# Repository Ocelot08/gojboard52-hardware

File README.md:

# gojboard52 hardware

Hardware files for **gojboard52**, a split wireless keyboard built around two nice!nano v2 controllers. The right
half carries a capacitive touch-bar slider (Microchip AT42QT2120); the left half carries a nice!view display
(an OLED footprint is also on the board).

Firmware lives in its own repository: https://github.com/Ocelot08/gojboard52-zmk

> Work in progress. Build notes are still to come.

## Photos

| | |
| --- | --- |
|  |  |

## Contents

| Folder | What is in it |
| --- | --- |
| `pcb/main-board/` | Keyboard PCB, KiCad 10 project (`BTSplit.kicad_pro`), STEP model, and fabrication gerbers (`gerber/`, zipped as `GojBoardV2-2_gerbers.zip`) |
| `pcb/touch-bar/` | Touch-bar PCB, KiCad project (`BTSplit_Touch.kicad_pro`), STEP model, and gerbers (`gerber/`, zipped as `GBTouchV0-3_gerbers.zip`) |
| `pcb/libs/` | The custom symbols and footprints these boards use (the double-sided SMD footprints, the pro micro and OLED footprints, the logo graphics) |
| `case/step/` | Case top and bottom (V4b) and a test plate, as STEP |
| `case/stl/` | Printable support parts: touch-bar support, nice!view support, alignment frame |
| `case/keycaps/` | Blank keycap and layer/mod keycap models |
| `docs/` | AT42QT2120 datasheet |
| `photos/` | The photos shown in this README |

The editable Rhino (`.3dm`) case models are not in this repository because of their size (40 MB or more each).

## PCB notes

- Project files are named `BTSplit` from the project's earlier name. The board is the gojboard52.
- Main board: 28 switch positions per board (Kailh low-profile, reversible footprint), through-hole diodes,
  1206 hand-solder resistors and capacitors, a pro-micro-pattern socket for the nice!nano, and double-sided SMD
  footprints (reset switch, power switch, resistors, capacitors) so they can be placed on either side.
- Reset switch: Panasonic EVQ-PUA02K. Power switch: Alps SSSS811101.
- Touch bar: three-electrode slider mode, six 1206 resistors, all 4.7 kΩ as built.
- Schematics and boards embed the symbols and footprints they use, so the projects open without extra setup. To edit
  parts, add `pcb/libs/01_Symbols.kicad_sym` and `pcb/libs/gojboard52.pretty` as libraries in KiCad.
- The BOM CSV exported from KiCad is out of date and is not included.

## Ordering

Upload the gerber zip for the board to the PCB fab of your choice (1.6 mm, 2 layers).

## License

Not yet chosen.

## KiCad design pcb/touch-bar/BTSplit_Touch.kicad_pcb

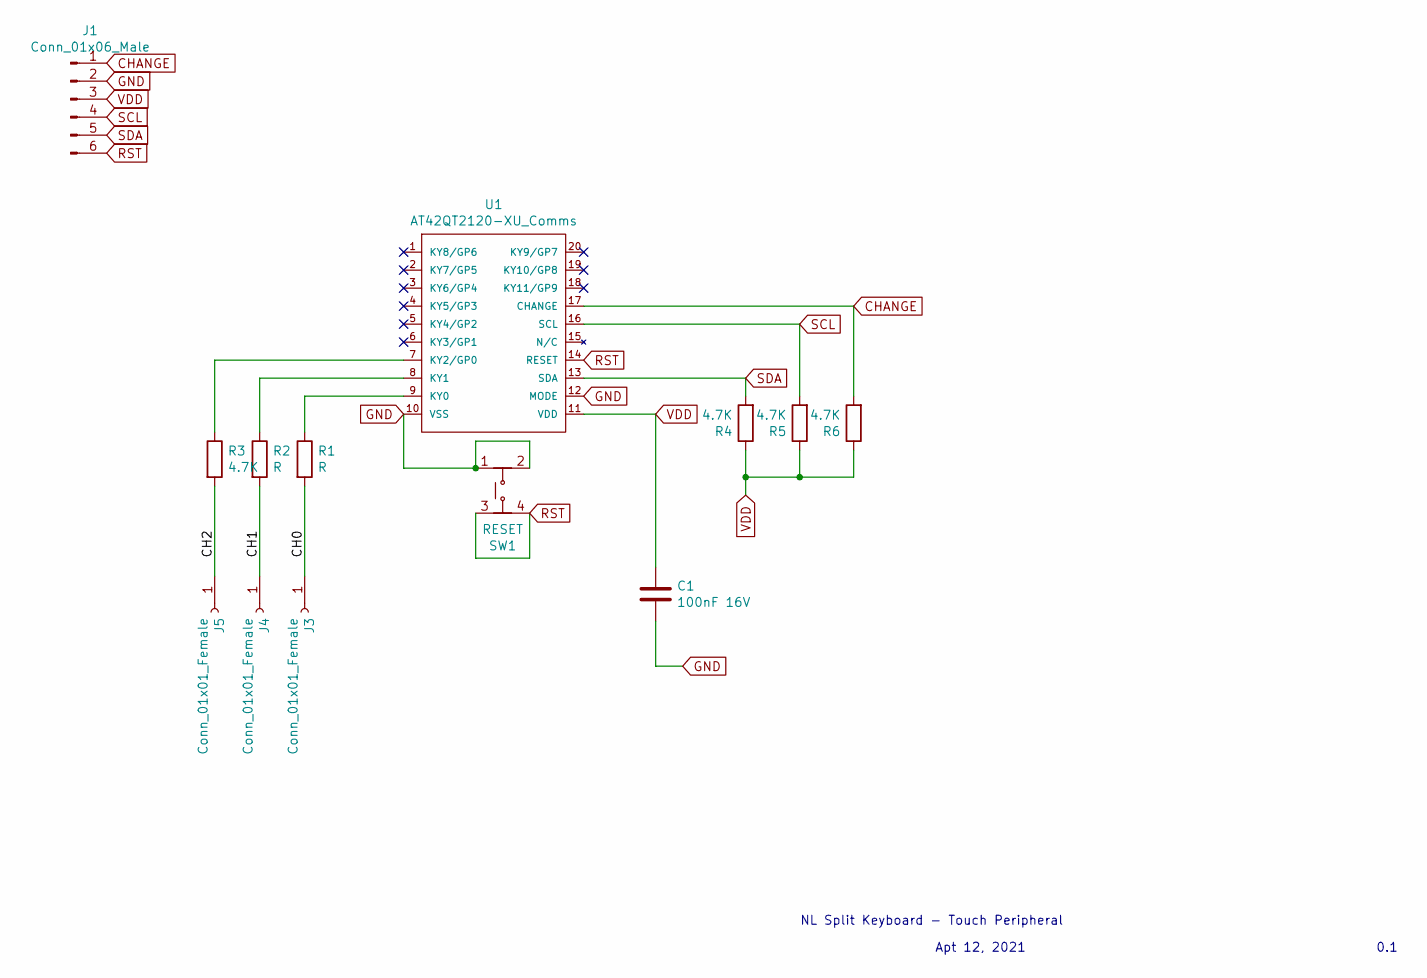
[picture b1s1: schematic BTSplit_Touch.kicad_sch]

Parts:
C1: 100nF 16V; C_1206_3216Metric
J1: Conn_01x06_Male; PinHeader_1x06_P2.54mm_Vertical
J3, J4, J5: Conn_01x01_Female; 1pad
R1, R2: R; R_1206_3216Metric_Pad1.30x1.75mm_HandSolder
R3, R4, R5, R6: 4.7K; R_1206_3216Metric_Pad1.30x1.75mm_HandSolder
SW1: RESET; PTS526 Switch
U1: AT42QT2120-XU_Comms; AT42QT2120-XUR

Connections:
/CH0: J3.1 (Pin_1_1), R1.2
/CH1: J4.1 (Pin_1_1), R2.2
/CH2: J5.1 (Pin_1_1), R3.2
CHANGE: J1.1, R6.2, U1.17 (CHANGE)
GND: C1.2, J1.2, SW1.1, SW1.2, U1.10 (VSS), U1.12 (MODE)
unnamed: R1.1, U1.9 (KY0)
unnamed: R2.1, U1.8 (KY1)
unnamed: R3.1, U1.7 (KY2/GP0)
RST: J1.6, SW1.3, SW1.4, U1.14 (RESET)
SCL: J1.4, R5.2, U1.16 (SCL)
SDA: J1.5, R4.2, U1.13 (SDA)
VDD: C1.1, J1.3, R4.1, R5.1, R6.1, U1.11 (VDD)

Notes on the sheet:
0.1
Apt 12, 2021
NL Split Keyboard - Touch Peripheral

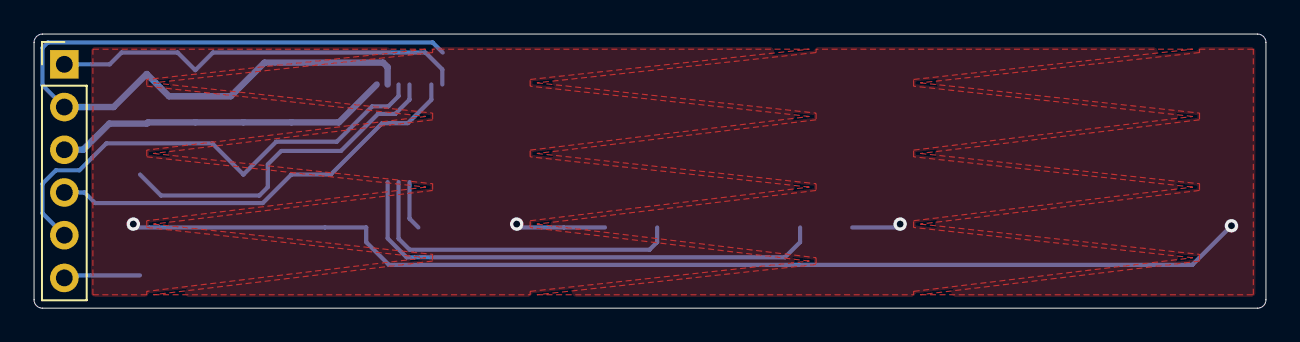
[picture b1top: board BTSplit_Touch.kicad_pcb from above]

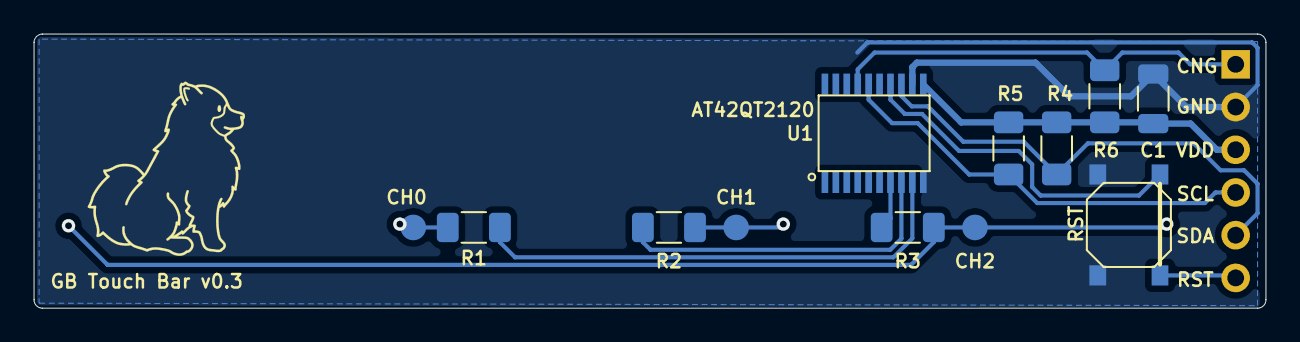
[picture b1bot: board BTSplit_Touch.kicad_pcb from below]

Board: 2 copper layers, 73.2 x 16.3 mm, 14 parts (13 on the bottom side), 12 nets.

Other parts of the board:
G2: Graphic; Goji10

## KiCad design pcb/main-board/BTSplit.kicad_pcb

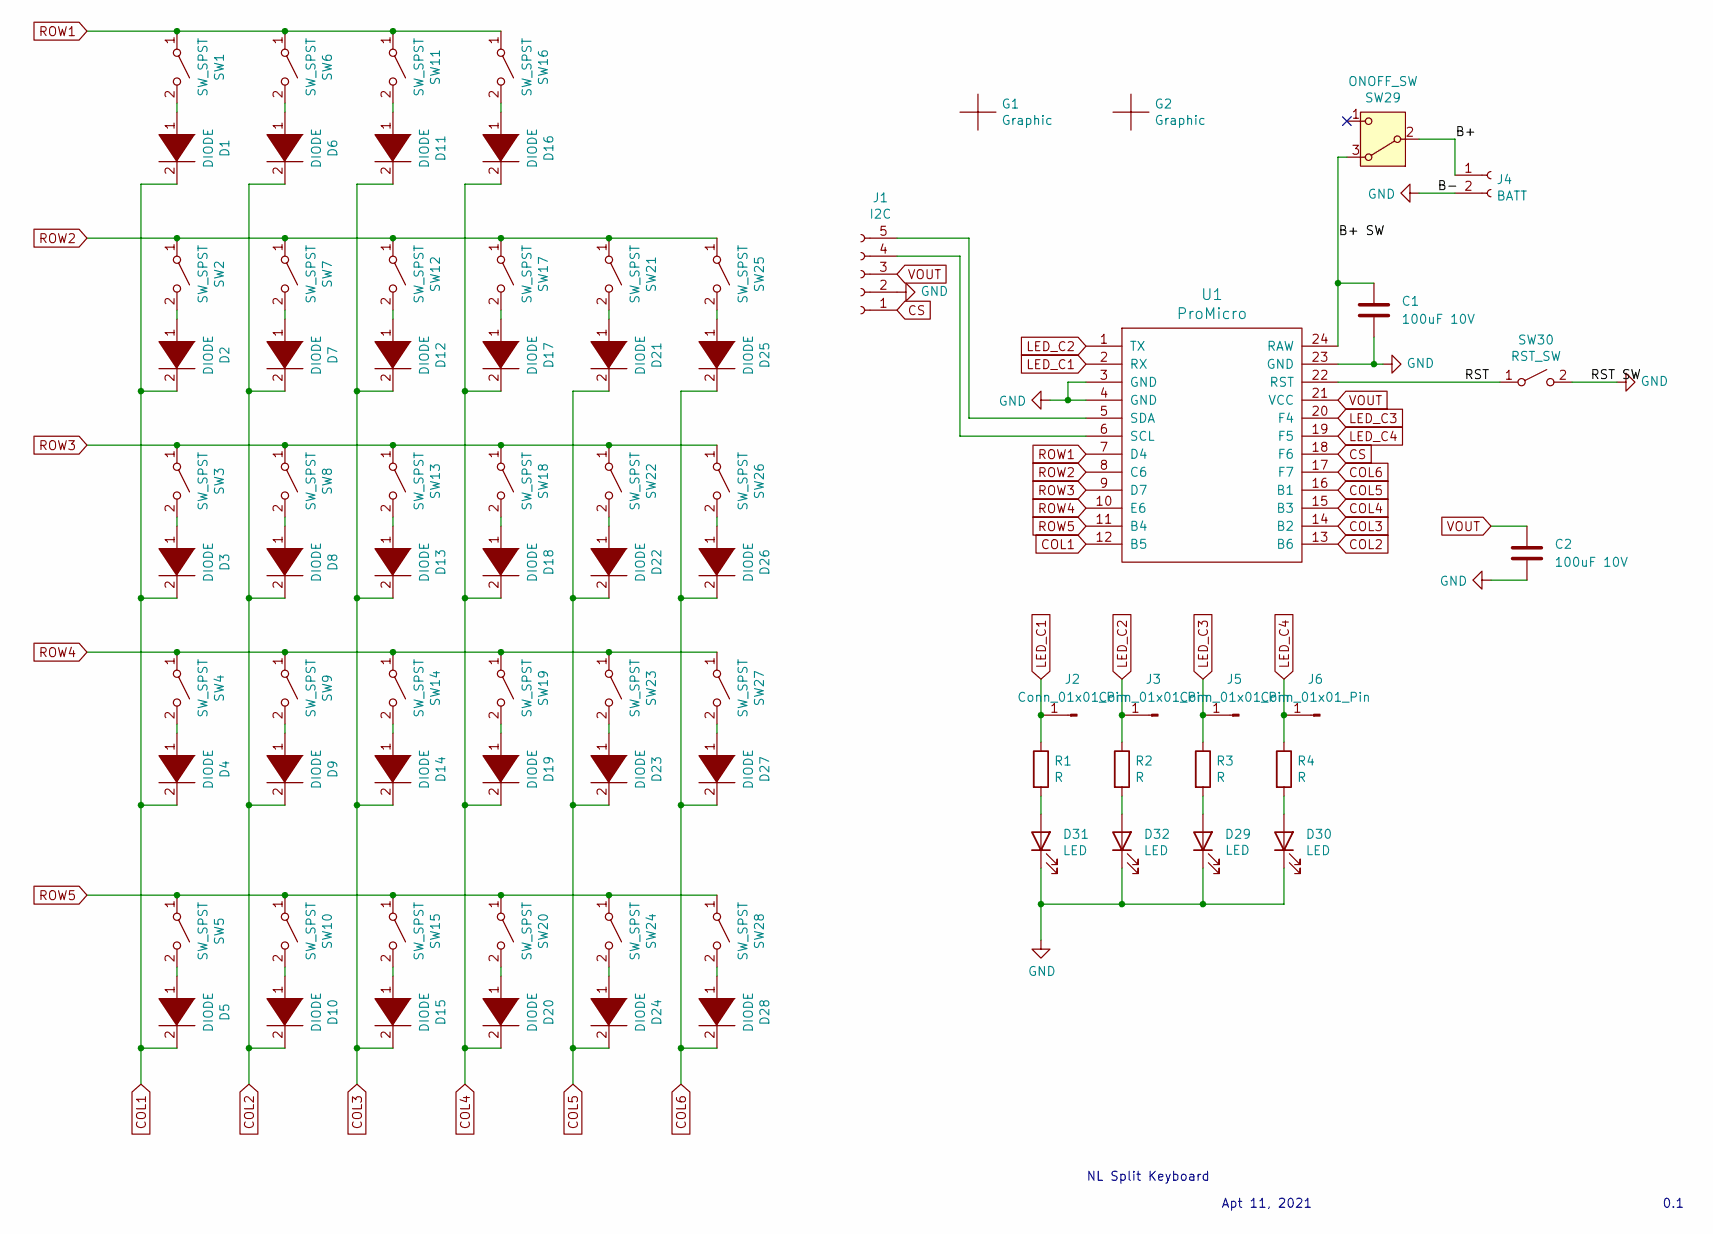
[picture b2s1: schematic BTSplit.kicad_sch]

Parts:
C1, C2: 100uF 10V; C_1206_HandSolder_DoubleSided
D1, D2, D3, D4, D5, D6, D7, D8, D9, D10, D11, D12, D13, D14, D15, D16, D17, D18, D19, D20, D21, D22, D23, D24, D25, D26, D27, D28: DIODE; D_DO-35_SOD27_P7.62mm_Horizontal
D29, D30, D31, D32: LED; LED_D1.8mm_W3.3mm_H2.4mm
G1: Graphic; Goji15
G2: Graphic; Goj30
J1: I2C; PinSocket_1x05_P2.54mm_Vertical
J2, J3, J5, J6: Conn_01x01_Pin; 1pad_DoubleSided
J4: BATT; PinHeader_1x02_P2.00mm_Vertical
R1, R2, R3, R4: R; R_1206_HandSolder_DoubleSided
SW1, SW2, SW3, SW4, SW5, SW6, SW7, SW8, SW9, SW10, SW11, SW12, SW13, SW14, SW15, SW16, SW17, SW18, SW19, SW20, SW21, SW22, SW23, SW24, SW25, SW26, SW27, SW28: SW_SPST; SW_Kailh_Choc_V1V2_flip
SW29: ONOFF_SW; SW4_SSSS811101_ALPS_DoubleSided
SW30: RST_SW; Panasonic_EVQPUJ_EVQPUA_DoubleSided
U1: ProMicro; ArduinoProMicro

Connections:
/B+: J4.1, SW29.2 (B)
/B+ SW: C1.1, SW29.3 (A), U1.24 (RAW)
/RST: SW30.1 (A), U1.22 (RST)
COL1: D1.2 (A), D2.2 (A), D3.2 (A), D4.2 (A), D5.2 (A), U1.12 (B5)
COL2: D6.2 (A), D7.2 (A), D8.2 (A), D9.2 (A), D10.2 (A), U1.13 (B6)
COL3: D11.2 (A), D12.2 (A), D13.2 (A), D14.2 (A), D15.2 (A), U1.14 (B2)
COL4: D16.2 (A), D17.2 (A), D18.2 (A), D19.2 (A), D20.2 (A), U1.15 (B3)
COL5: D21.2 (A), D22.2 (A), D23.2 (A), D24.2 (A), U1.16 (B1)
COL6: D25.2 (A), D26.2 (A), D27.2 (A), D28.2 (A), U1.17 (F7)
CS: J1.1, U1.18 (F6)
GND: C1.2, C2.2, D29.1 (K), D30.1 (K), D31.1 (K), D32.1 (K), J1.2, J4.2, SW30.2 (B), U1.3 (GND), U1.4 (GND), U1.23 (GND)
LED_C1: J2.1 (Pin_1_1), R1.1, U1.2 (RX)
LED_C2: J3.1 (Pin_1_1), R2.1, U1.1 (TX)
LED_C3: J5.1 (Pin_1_1), R3.1, U1.20 (F4)
LED_C4: J6.1 (Pin_1_1), R4.1, U1.19 (F5)
unnamed: D1.1 (K), SW1.2 (B)
unnamed: D2.1 (K), SW2.2 (B)
unnamed: D3.1 (K), SW3.2 (B)
unnamed: D4.1 (K), SW4.2 (B)
unnamed: D5.1 (K), SW5.2 (B)
unnamed: D6.1 (K), SW6.2 (B)
unnamed: D7.1 (K), SW7.2 (B)
unnamed: D8.1 (K), SW8.2 (B)
unnamed: D9.1 (K), SW9.2 (B)
unnamed: D10.1 (K), SW10.2 (B)
unnamed: D11.1 (K), SW11.2 (B)
unnamed: D12.1 (K), SW12.2 (B)
unnamed: D13.1 (K), SW13.2 (B)
unnamed: D14.1 (K), SW14.2 (B)
unnamed: D15.1 (K), SW15.2 (B)
unnamed: D16.1 (K), SW16.2 (B)
unnamed: D17.1 (K), SW17.2 (B)
unnamed: D18.1 (K), SW18.2 (B)
unnamed: D19.1 (K), SW19.2 (B)
unnamed: D20.1 (K), SW20.2 (B)
unnamed: D21.1 (K), SW21.2 (B)
unnamed: D22.1 (K), SW22.2 (B)
unnamed: D23.1 (K), SW23.2 (B)
unnamed: D24.1 (K), SW24.2 (B)
unnamed: D25.1 (K), SW25.2 (B)
unnamed: D26.1 (K), SW26.2 (B)
unnamed: D27.1 (K), SW27.2 (B)
unnamed: D28.1 (K), SW28.2 (B)
unnamed: D29.2 (A), R3.2
unnamed: D30.2 (A), R4.2
unnamed: D31.2 (A), R1.2
unnamed: D32.2 (A), R2.2
unnamed: J1.4, U1.6 (SCL)
unnamed: J1.5, U1.5 (SDA)
ROW1: SW1.1 (A), SW6.1 (A), SW11.1 (A), SW16.1 (A), U1.7 (D4)
ROW2: SW2.1 (A), SW7.1 (A), SW12.1 (A), SW17.1 (A), SW21.1 (A), SW25.1 (A), U1.8 (C6)
ROW3: SW3.1 (A), SW8.1 (A), SW13.1 (A), SW18.1 (A), SW22.1 (A), SW26.1 (A), U1.9 (D7)
ROW4: SW4.1 (A), SW9.1 (A), SW14.1 (A), SW19.1 (A), SW23.1 (A), SW27.1 (A), U1.10 (E6)
ROW5: SW5.1 (A), SW10.1 (A), SW15.1 (A), SW20.1 (A), SW24.1 (A), SW28.1 (A), U1.11 (B4)
VOUT: C2.1, J1.3, U1.21 (VCC)

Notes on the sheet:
NL Split Keyboard
0.1
Apt 11, 2021

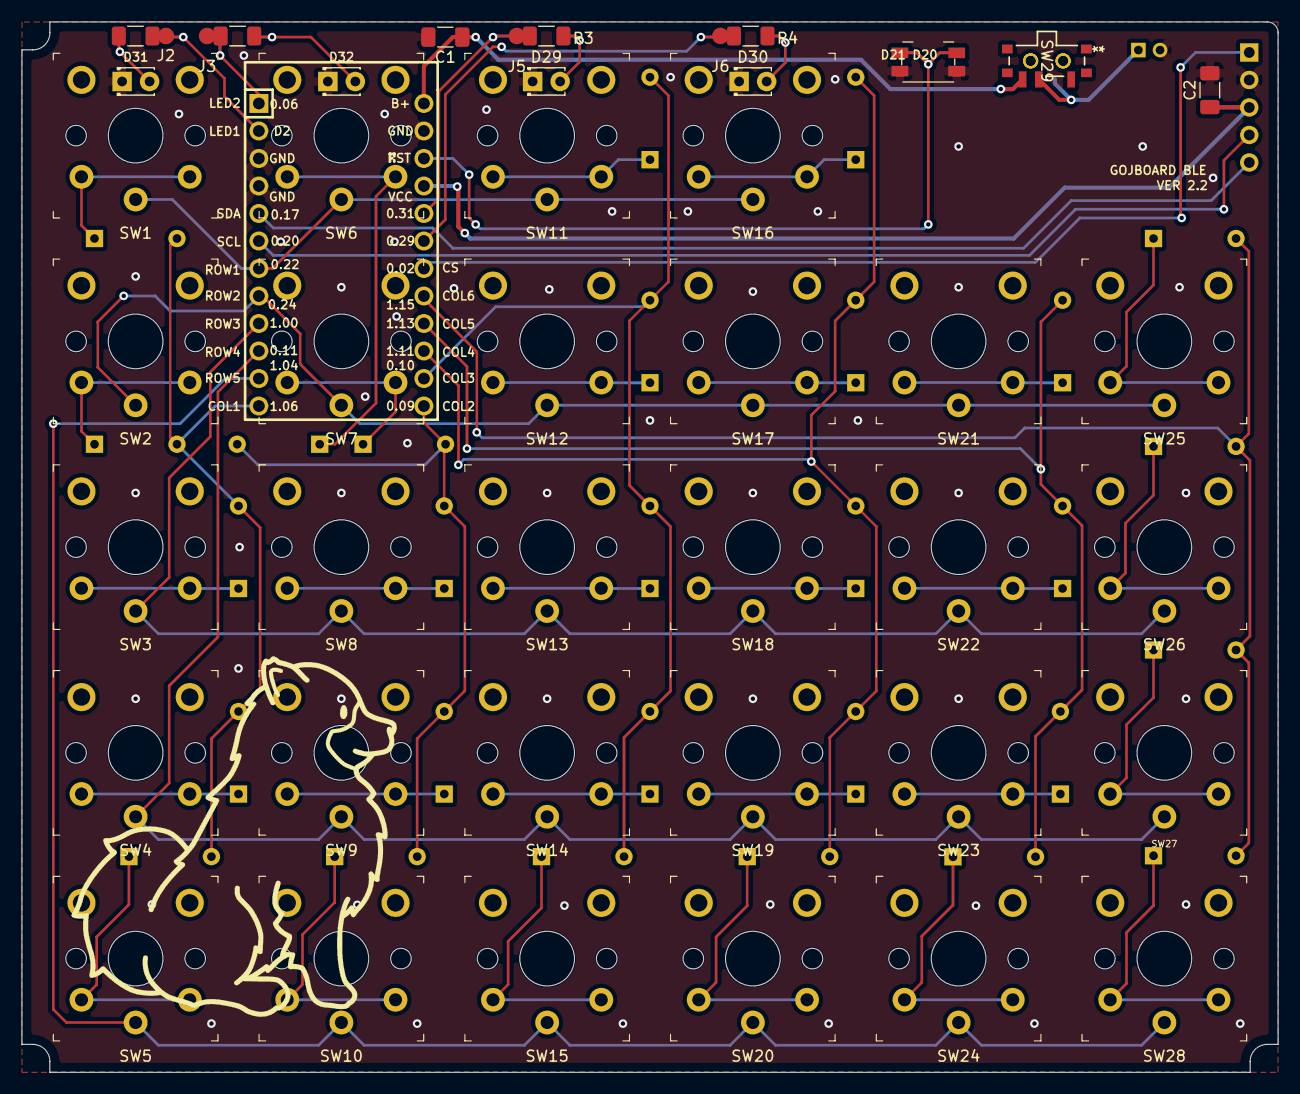
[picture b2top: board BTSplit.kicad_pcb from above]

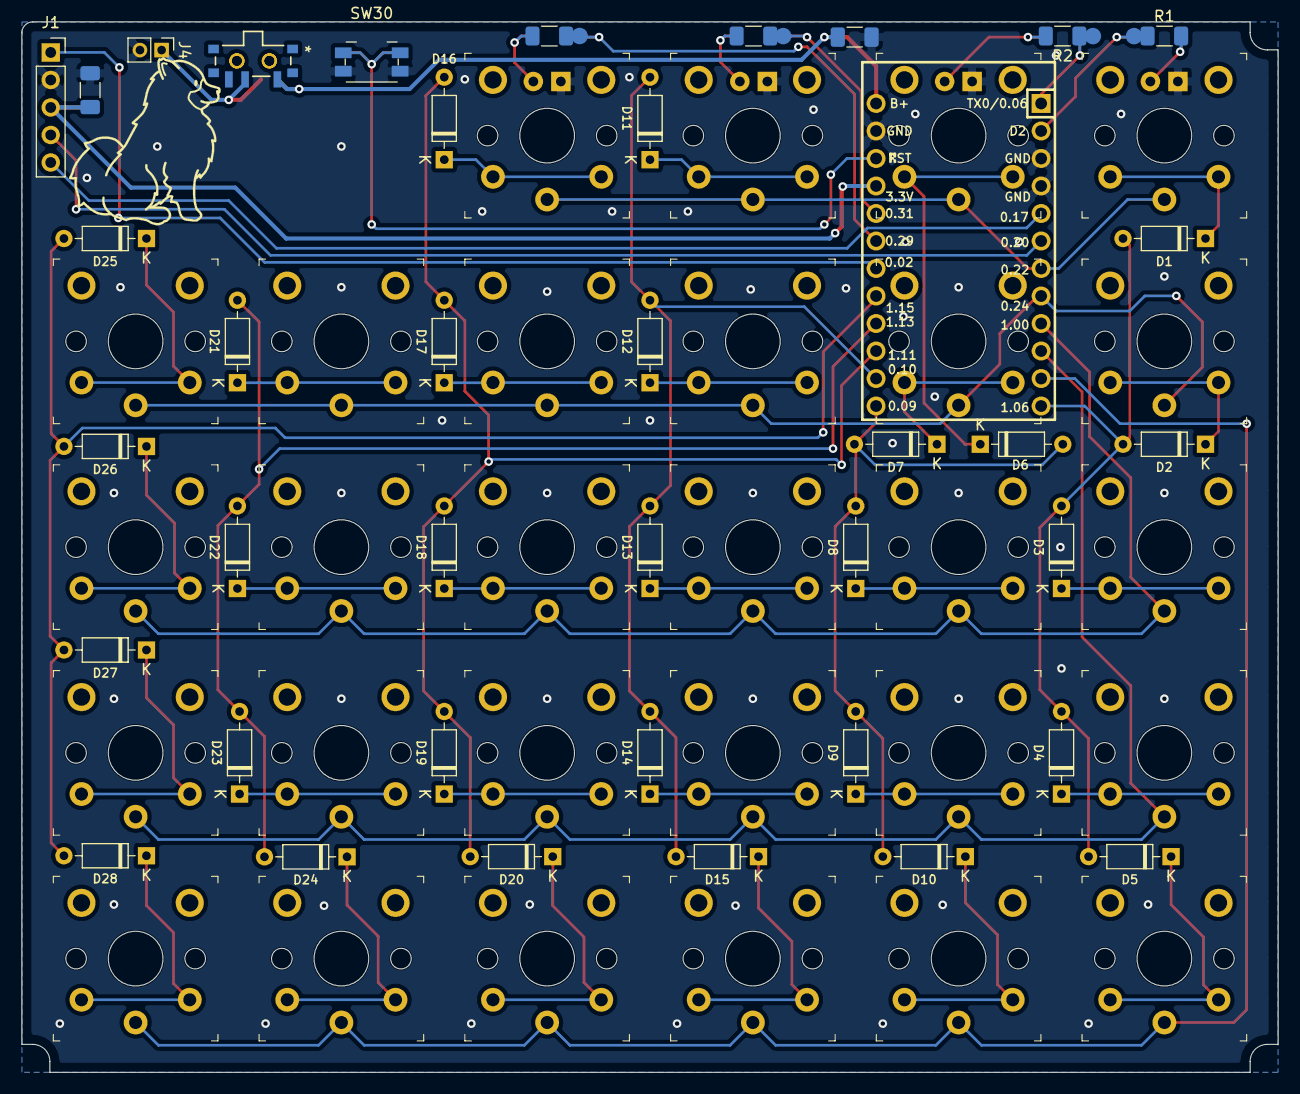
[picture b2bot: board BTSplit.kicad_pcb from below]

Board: 2 copper layers, 116.0 x 97.0 mm, 77 parts (34 on the bottom side), 55 nets.
